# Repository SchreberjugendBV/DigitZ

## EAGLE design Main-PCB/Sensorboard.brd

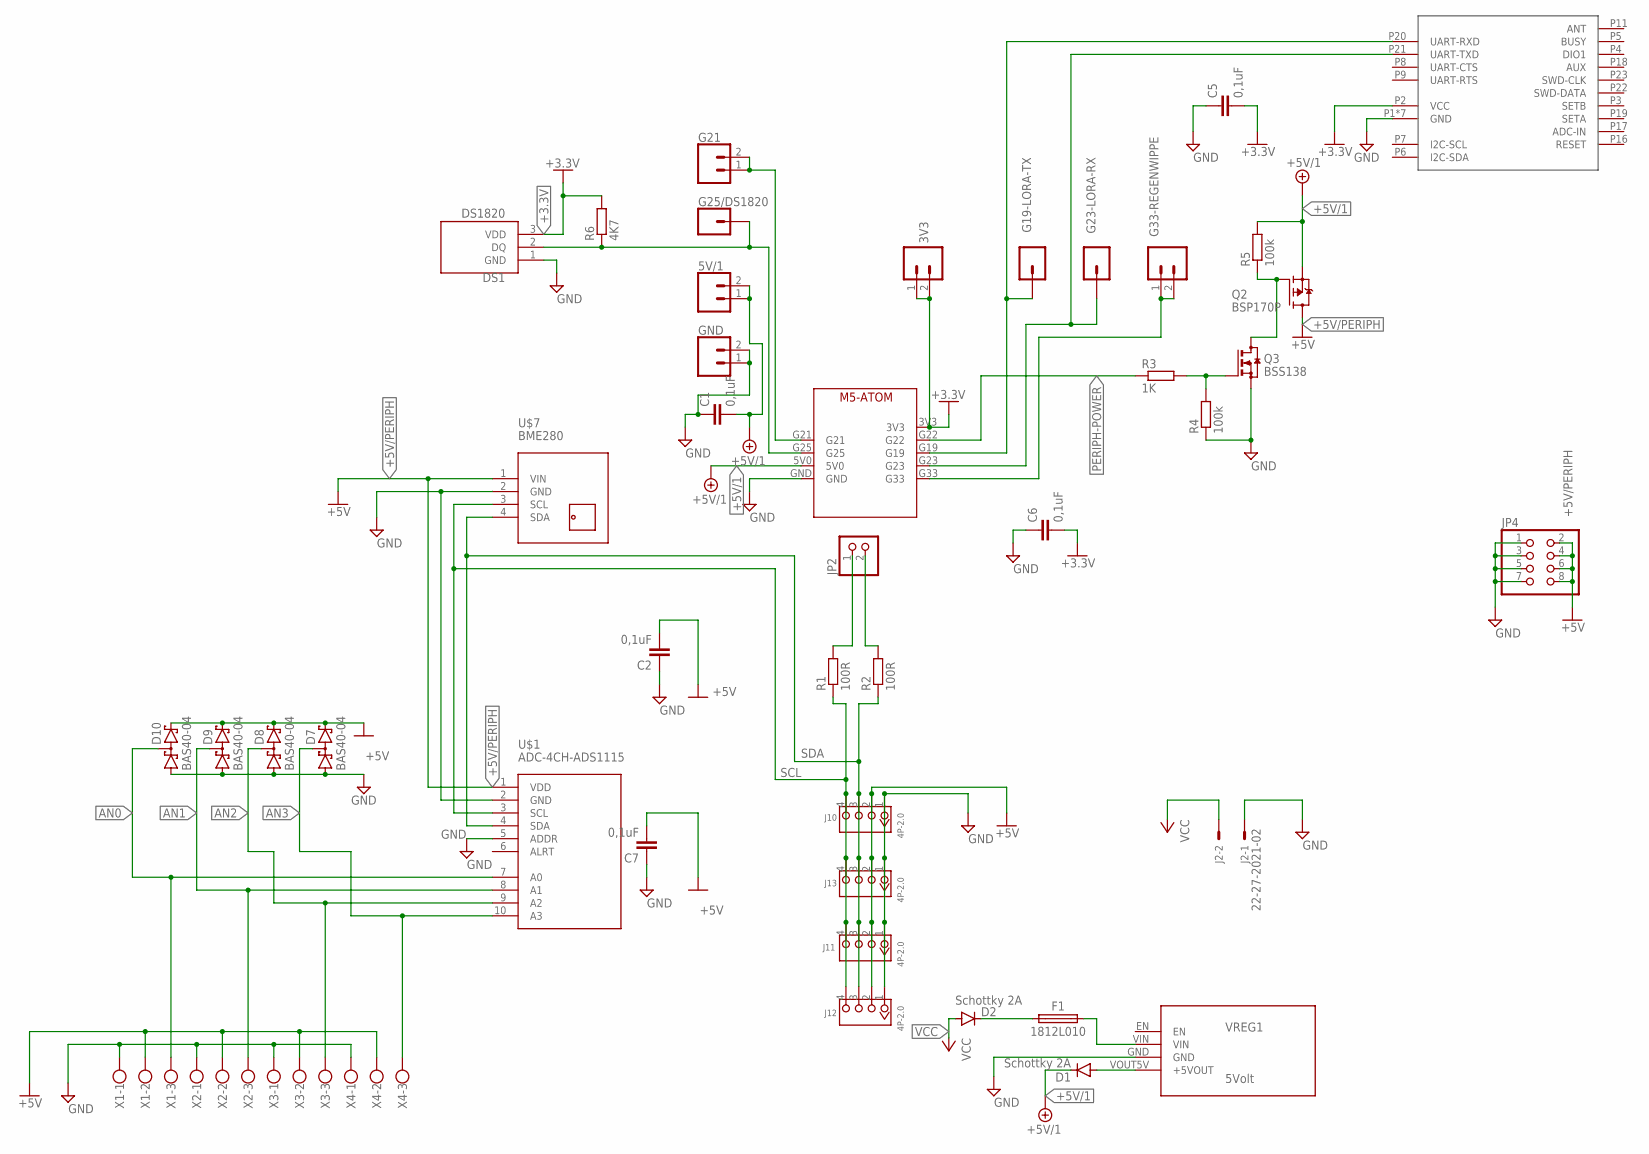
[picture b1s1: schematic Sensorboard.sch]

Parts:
3V3, 5V/1: CONN_02; 1X02
C1, C2, C5, C6, C7: 0,1uF; C025-025X050
D1, D2: Schottky 2A; DO41-10
D7, D8, D9, D10: BAS40-04; SOT23
DS1: DS1820; DS1820-TO92
F1: 1812L010; FUSC4532X125
G19-LORA-TX, G23-LORA-RX, G25/DS1820: CONN_01; 1X01
G21, G33-REGENWIPPE: CONN_02; 1X02
GND: CONN_02; 1X02
J2: 22-27-2021-02; 6410-02
J10, J11, J12, J13: 4P-2.0; HW4-2.0
JP2: PINHD-1X2; 1X02
JP4: PINHD-2X4; 2X04
M5-ATOM: M5-ATOM
Q2: BSP170P; SOT223
Q3: BSS138; SOT23
R1, R2: 100R; 0204/7
R3: 1K; R1206
R4, R5: 100k; R1206
R6: 4K7; R1206
U$1: ADC-4CH-ADS1115
U$2: E78-868LN22S
U$7: BME280; TEMP-HUM-PRES-BME280
VREG1: 5Volt; VREG-STEPDOWN
X1, X2, X3, X4: W237-103-RB

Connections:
+3.3V: 3V3.1, 3V3.2, C5.2, C6.2, DS1.3 (VDD), M5-ATOM.3V3, R6.2, U$2.P2 (VCC)
+5V/1: 5V/1.1, 5V/1.2, C1.2, D1.C, M5-ATOM.5V0, Q2.3 (S), R5.2
+5V/PERIPH: C2.2, C7.2, D7.2 (C2), D8.2 (C2), D9.2 (C2), D10.2 (C2), J10.2, J11.2, J12.2, J13.2, JP4.2, JP4.4, JP4.6, JP4.8, Q2.2 (D), Q2.4 (D), U$1.1 (VDD), U$7.1 (VIN), X1.2, X2.2, X3.2, X4.2
AN0: D10.3 (C1A2), U$1.7 (A0), X1.3
AN1: D9.3 (C1A2), U$1.8 (A1), X2.3
AN2: D8.3 (C1A2), U$1.9 (A2), X3.3
AN3: D7.3 (C1A2), U$1.10 (A3), X4.3
GND: C1.1, C2.1, C5.1, C6.1, C7.1, D7.1 (A1), D8.1 (A1), D9.1 (A1), D10.1 (A1), DS1.1 (GND), GND.1, GND.2, J2.1, J10.1, J11.1, J12.1, J13.1, JP4.1, JP4.3, JP4.5, JP4.7, M5-ATOM.GND, Q3.2 (S), R4.1, U$1.2 (GND), U$1.5 (ADDR), U$2.P1 (GND), U$2.P10 (GND), U$2.P12 (GND), U$2.P13 (GND), U$2.P14 (GND), U$2.P15 (GND), U$2.P24 (GND), U$7.2 (GND), VREG1.GND, X1.1, X2.1, X3.1, X4.1
LORA-RX: G23-LORA-RX.1, M5-ATOM.G23, U$2.P21 (UART-TXD)
LORA-TX: G19-LORA-TX.1, M5-ATOM.G19, U$2.P20 (UART-RXD)
unnamed: G33-REGENWIPPE.1, G33-REGENWIPPE.2, M5-ATOM.G33
unnamed: JP2.1, R1.2
unnamed: DS1.2 (DQ), G25/DS1820.1, M5-ATOM.G25, R6.1
unnamed: G21.1, G21.2, M5-ATOM.G21
unnamed: JP2.2, R2.2
unnamed: D1.A, VREG1.VOUT5V (+5VOUT)
unnamed: Q3.1 (G), R3.2, R4.2
unnamed: D2.C, F1.1
unnamed: F1.2, VREG1.VIN
unnamed: Q2.1 (G), Q3.3 (D), R5.1
PERIPH-POWER: M5-ATOM.G22, R3.1
SCL: J10.4, J11.4, J12.4, J13.4, R1.1, U$1.3 (SCL), U$7.3 (SCL)
SDA: J10.3, J11.3, J12.3, J13.3, R2.1, U$1.4 (SDA), U$7.4 (SDA)
VCC: D2.A, J2.2

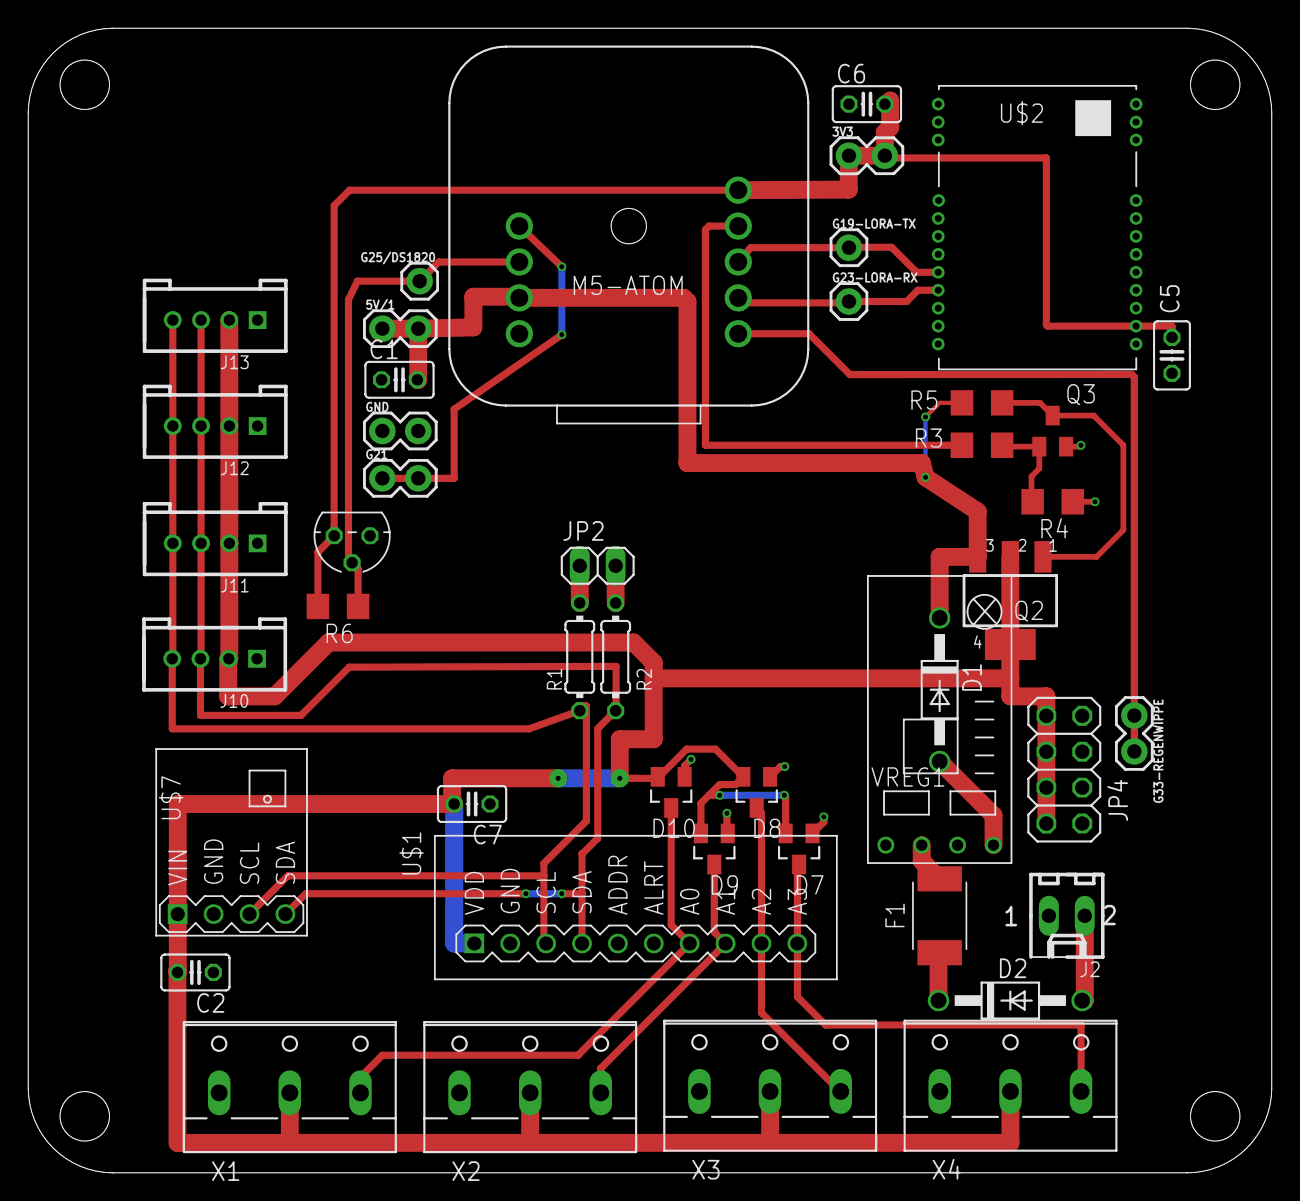
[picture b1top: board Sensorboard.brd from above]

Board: 2 copper layers, 88.0 x 81.0 mm, 45 parts (0 on the bottom side), 24 nets.

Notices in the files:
parts and their libraries:
SparkFun-Connectors: Licensing: Creative Commons ShareAlike 4.0 International - https://creativecommons.org/licenses/by-sa/4.0
RB-diy-modules: Released under the Creative Commons Attribution 4.0 International License: http://creativecommons.org/licenses/by/4.0
